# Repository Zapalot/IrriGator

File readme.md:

This is the irrigation scheduler currently under development.

It consists of..
- one (and possibly later multiple) PCB designs in KiCad
- An Arduino Program for ESP32

It depends on

- ArduPar3
- ArduParWeb

When finished, it will provide the following functionality:

- Actuating solenoid valves, fans, lights and other actuators based on schedules and/or sensor measurements
- Web interface for configuring schedules and other settings
- logging and display of sensor data
- external RTC support for hassle free time keeping

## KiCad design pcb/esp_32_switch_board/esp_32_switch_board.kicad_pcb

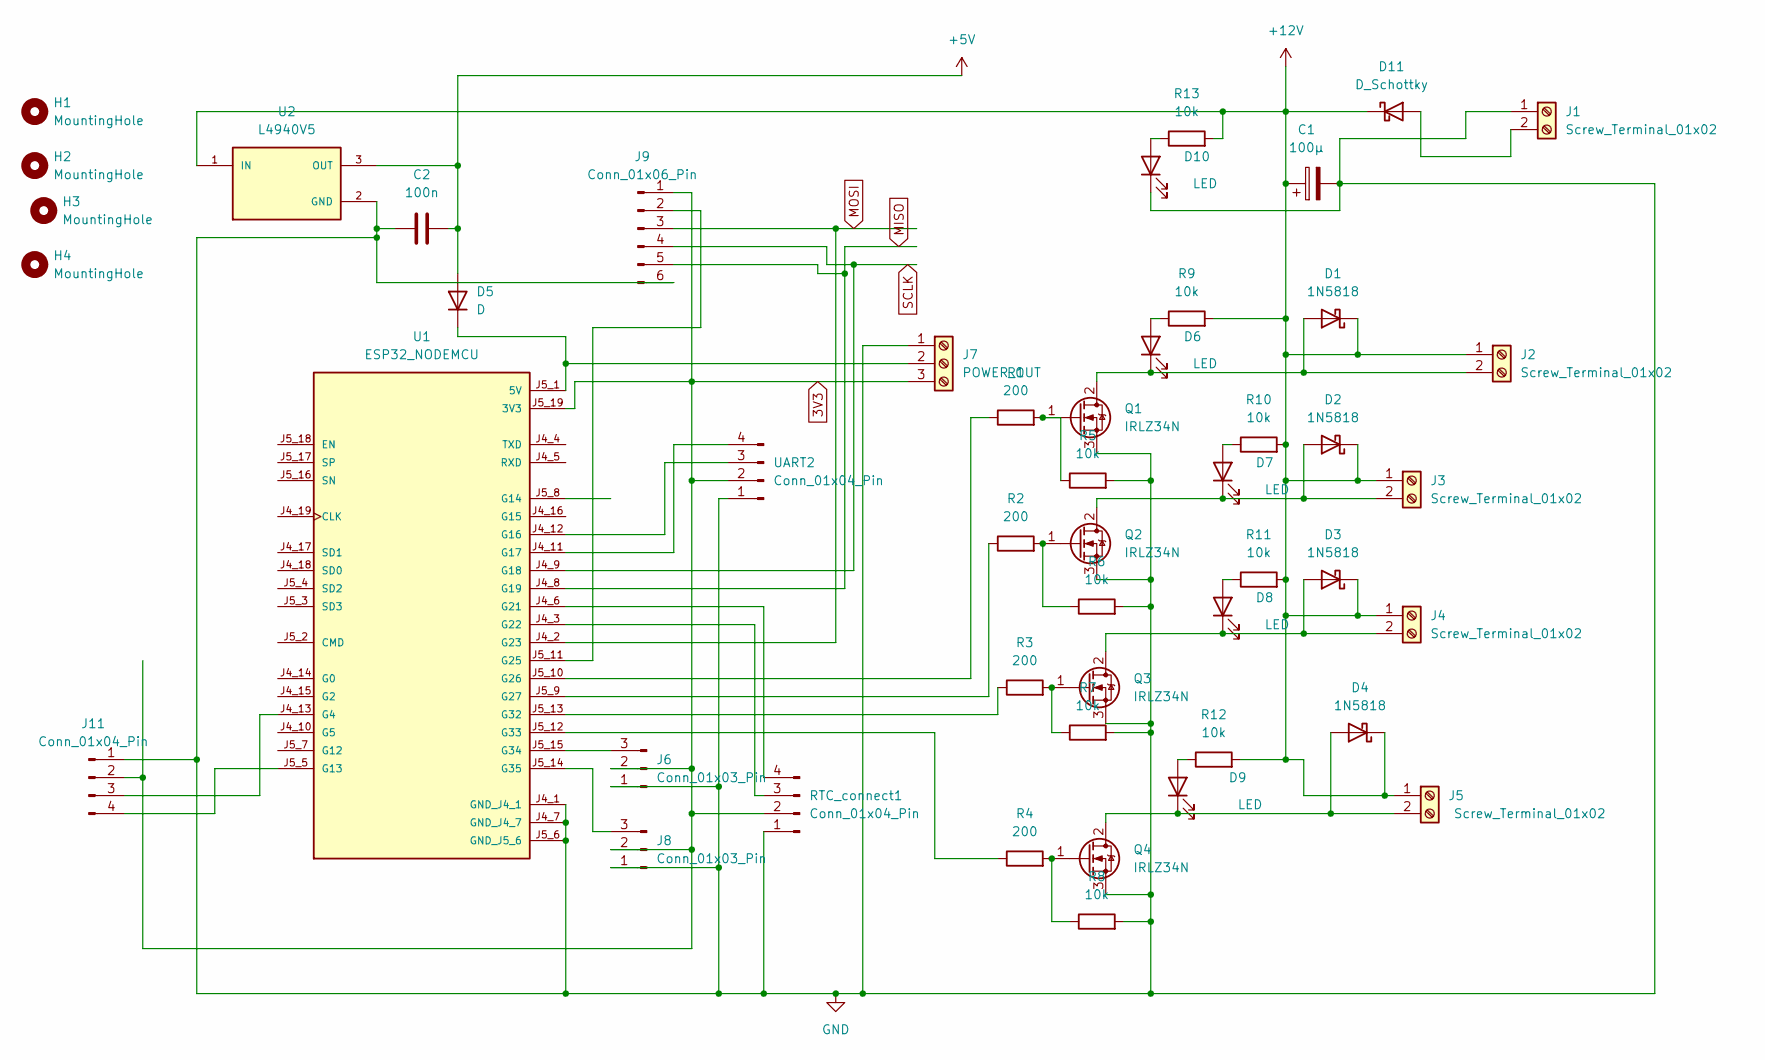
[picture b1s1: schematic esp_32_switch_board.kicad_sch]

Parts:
C1: 100µ; CP_Radial_D8.0mm_P2.50mm
C2: 100n; C_Disc_D5.0mm_W2.5mm_P5.00mm
D1, D2, D3, D4: 1N5818; D_DO-41_SOD81_P10.16mm_Horizontal
D5: D; D_DO-15_P10.16mm_Horizontal
D6, D7, D8, D9, D10: LED; LED_D3.0mm
D11: D_Schottky; D_DO-201AD_P15.24mm_Horizontal
H1, H2, H3, H4: MountingHole; MountingHole_3.2mm_M3_ISO14580_Pad
J1, J2, J3, J4, J5: Screw_Terminal_01x02; TerminalBlock_MetzConnect_Type101_RT01602HBWC_1x02_P5.08mm_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
J6, J8: Conn_01x03_Pin; JST_XH_B3B-XH-A_1x03_P2.50mm_Vertical
J7: POWER_OUT; TerminalBlock_MetzConnect_Type101_RT01603HBWC_1x03_P5.08mm_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
J9: Conn_01x06_Pin; PinHeader_1x06_P2.54mm_Vertical
J11: Conn_01x04_Pin; JST_XA_B04B-XASK-1_1x04_P2.50mm_Vertical
Q1, Q2, Q3, Q4: IRLZ34N; TO-220-3_Vertical
R1, R2, R3, R4: 200; R_Axial_DIN0207_L6.3mm_D2.5mm_P10.16mm_Horizontal
R5, R6, R7, R8, R9, R10, R11, R12, R13: 10k; R_Axial_DIN0207_L6.3mm_D2.5mm_P10.16mm_Horizontal
RTC_connect1: Conn_01x04_Pin; PinHeader_1x04_P2.54mm_Vertical
U1: ESP32_NODEMCU; MODULE_ESP32_NODEMCU
U2: L4940V5; TO225P1040X460X1968-3; PARTREV 14
UART2: Conn_01x04_Pin; JST_XA_B04B-XASK-1_1x04_P2.50mm_Vertical

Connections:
3V3: J6.2, J7.3, J8.2, J9.1, J11.2, RTC_connect1.2, U1.J5_19 (3V3), UART2.2
+5V: C2.2, D5.2 (A), U2.3 (OUT)
+12V: C1.1, D1.1 (K), D2.1 (K), D3.1 (K), D4.1 (K), D11.1 (K), J2.1, J3.1, J4.1, J5.1, R9.2, R10.2, R11.2, R12.2, R13.2, U2.1 (IN)
GND: C1.2, C2.1, D10.1 (K), J1.1, J6.1, J7.1, J8.1, J9.6, J11.1, Q1.3 (S), Q2.3 (S), Q3.3 (S), Q4.3 (S), R5.2, R6.2, R7.2, R8.2, RTC_connect1.1, U1.J4_1 (GND_J4_1), U1.J4_7 (GND_J4_7), U1.J5_6 (GND_J5_6), U2.2 (GND), UART2.1
MISO: J9.5, U1.J4_8 (G19)
MOSI: J9.3, U1.J4_2 (G23)
unnamed: D1.2 (A), D6.1 (K), J2.2, Q1.2 (D)
unnamed: D2.2 (A), D7.1 (K), J3.2, Q2.2 (D)
unnamed: D3.2 (A), D8.1 (K), J4.2, Q3.2 (D)
unnamed: D4.2 (A), D9.1 (K), J5.2, Q4.2 (D)
unnamed: D5.1 (K), J7.2, U1.J5_1 (5V)
unnamed: D6.2 (A), R9.1
unnamed: D7.2 (A), R10.1
unnamed: D8.2 (A), R11.1
unnamed: D9.2 (A), R12.1
unnamed: D10.2 (A), R13.1
unnamed: D11.2 (A), J1.2
unnamed: J6.3, U1.J5_15 (G34)
unnamed: J8.3, U1.J5_14 (G35)
unnamed: J9.2, U1.J5_11 (G25)
unnamed: J11.3, U1.J4_13 (G4)
unnamed: J11.4, U1.J5_5 (G13)
unnamed: Q1.1 (G), R1.2, R5.1
unnamed: Q2.1 (G), R2.2, R6.1
unnamed: Q3.1 (G), R3.2, R7.1
unnamed: Q4.1 (G), R4.2, R8.1
unnamed: RTC_connect1.3, U1.J4_3 (G22)
unnamed: RTC_connect1.4, U1.J4_6 (G21)
unnamed: U1.J4_12 (G16), UART2.3
unnamed: U1.J4_11 (G17), UART2.4
unnamed: R1.1, U1.J5_10 (G26)
unnamed: R2.1, U1.J5_9 (G27)
unnamed: R3.1, U1.J5_13 (G32)
unnamed: R4.1, U1.J5_12 (G33)
SCLK: J9.4, U1.J4_9 (G18)

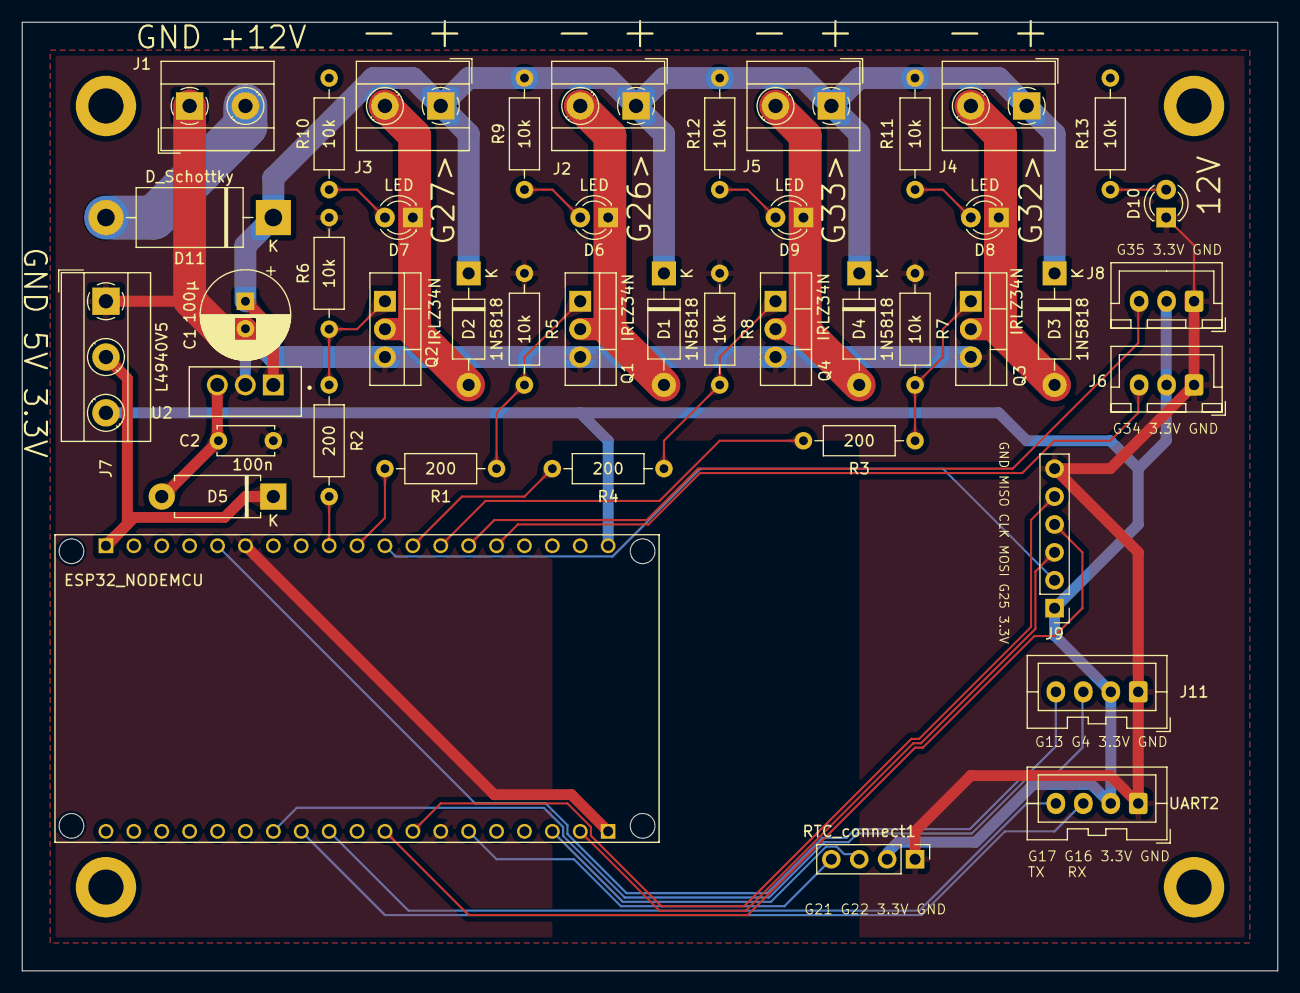
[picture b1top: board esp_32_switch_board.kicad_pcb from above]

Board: 2 copper layers, 114.3 x 86.4 mm, 48 parts (0 on the bottom side), 35 nets.

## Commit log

2024-06-18 first fully functional version
